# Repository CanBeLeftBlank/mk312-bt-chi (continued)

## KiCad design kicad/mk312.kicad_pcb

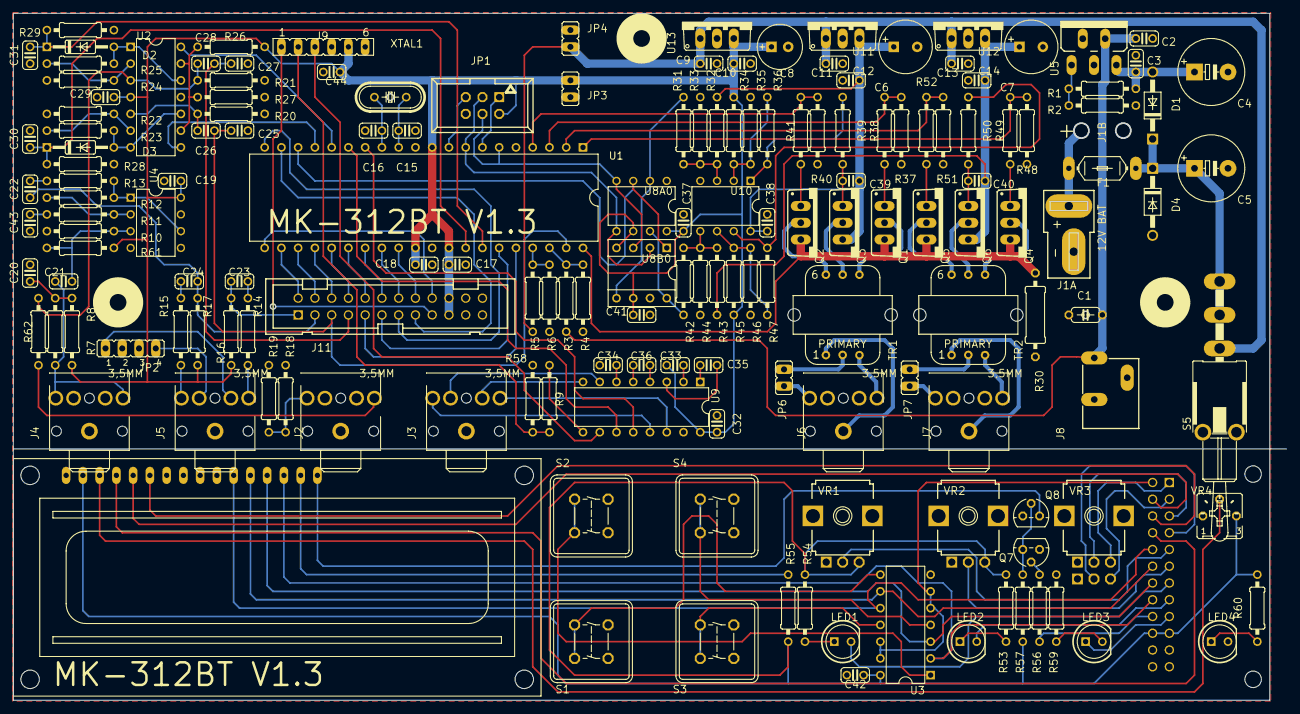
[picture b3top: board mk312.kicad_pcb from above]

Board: 2 copper layers, 193.0 x 104.1 mm, 170 parts (1 on the bottom side), 131 nets.

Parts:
@HOLE0, @HOLE1, @HOLE2, @HOLE3, @HOLE4: (no value)
C1: 10uF; C050-024X044
C2, C3, C9, C10, C11, C12, C13, C14, C17, C18, C19, C21, C26, C28, C29, C32, C37, C38, C39, C40, C41, C42, C44: 0.1uF; C025-024X044
C4, C5: 1000uF; E5-10,5
C6, C7: 470uF; E3,5-8
C8: 10uF; E2,5-7
C15, C16: 18pF; C025-024X044
C20, C22, C23, C24, C30, C31, C33, C34, C35, C36, C43: 1uF; C025-024X044
C25, C27: 1nF; C025-024X044
D1, D4: 1N4004; DO41-10
D2, D3: 1N4148DO35-10; DO35-10
F1: 1A POLY; LITTLEFUSE
J1: +12V BATTERY; DEANS
J2: REMOTE INPUT; STX3100
J3: LINK INPUT; STX3100
J4: MIC INPUT; STX3100
J5: LINE INPUT; STX3100
J6: OUTPUT A; STX3100
J7: OUTPUT B; STX3100
J8: VDC INPUT; POWER_JACK_SLOT
J9: RADIO INTERFACE; FE06
J10: 2524-; PAK100_2500-24
J11: FRONT PANEL; PAK100_2500-24
JP1: ISP; 057-006-1
JP2: AUX LINE IN; JP4
JP3: +5V; JP1
JP4: +12; JP1
JP6, JP7: JP1
LCD1: HD44780LCD-1602; LCD1602
LED1: OUTPUT A; LED5MM
LED2: OUTPUT B; LED5MM
LED3: RADIO; LED5MM
LED4: POWER; LED5MM
Q1, Q2, Q4, Q5: IRL520N; TO220V
Q3, Q6: IRF9Z24; TO220V
Q7, Q8: 2N3904; TO92
R1: 12K; 0207_10
R2: 1.2K; 0207_10
R3, R10, R20, R21, R27, R28, R29, R31, R32, R33, R34, R36, R37, R40, R42, R43, R44, R45, R47, R48, R51, R61: 100K; 0207_10
R4, R11, R16, R17, R22, R24: 20K; 0207_10
R5, R38, R39, R41, R49, R50, R52, R58: 10K; 0207_10
R6: 3.3K; 0207_10
R7, R8: 2.2K; 0207_10
R9, R13: 4.7K; 0207_10
R12, R23, R25, R26: 1M; 0207_10
R14, R15, R19, R62: 1K; 0207_10
R18, R56, R57: 1.5K; 0207_10
R30: 0.5R; 0309_12
R35, R46: 200K; 0207_10
R53, R54, R59, R60: 390; 0207_10
R55: 47; 0207_10
S1: OK; DTE6K
S2: MENU; DTE6K
S3: LEFT/DOWN; DTE6K
S4: RIGHT/UP; DTE6K
S5: POWER; LPV-1
TR1, TR2: 42TL004; 42TL
U1: ATMEGA16/32-P; DIL40
U2: LM324N; DIL14
U3: 4066N; DIL14
U4, U10: LM358N; DIL08
U5: LM2941T; TO220-5
U8A0: MAX548; DIL08
U8B0: LTC1661; SOCKET-08
U9: MAX232; DIL16
U11, U12: 7809TV; TO220V
U13: 7805TV; TO220V
VR1: LEVEL A; 9MM_SNAP-IN_POT
VR2: LEVEL B; 9MM_SNAP-IN_POT
VR3: MULTI-ADJ; DUAL_9MM_SNAP-IN_POT
VR4: LCD CONTRAST; B25P
XTAL1: 8.0 MHz; HC49_S

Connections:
+5V: C8.+, C10.1, C17.1, C18.1, C19.1, C29.1, C32.1, C33.1, C37.1, C41.1, C42.1, C44.1, J9.5, J10.19, J10.20, J11.19, J11.20, JP1.2, JP3.1, LCD1.2, R8.2, R16.2, R17.2, R18.2, R26.2, R34.2, R45.2, R53.2, R54.2, R55.2, R57.1, R60.2, R61.2, U1.10, U1.30, U1.32, U2.4, U3.14, U4.8, U8A0.6, U8A0.8, U8B0.4, U8B0.6, U9.16, U13.3, VR1.3, VR2.3, VR4.E
+8V: C6.+, C12.1, C38.1, C39.2, Q3.3, R32.2, U10.8, U11.3
+9V: C7.+, C14.1, C40.2, Q6.3, R43.2, U12.3
+12V: C9.1, C11.1, C13.1, JP4.1, R5.2, S5.1, U11.1, U12.1, U13.1
GND: C1.2, C2.2, C3.2, C4.-, C5.-, C6.-, C7.-, C8.-, C9.2, C10.2, C11.2, C12.2, C13.2, C14.2, C15.2, C16.2, C17.2, C18.2, C19.2, C20.2, C25.2, C27.2, C29.2, C30.2, C31.2, C32.2, C34.2, C37.2, C38.2, C41.2, C42.2, C43.2, C44.2, D4.A, J1.-, J2.1, J3.1, J4.1, J5.1, J8.GND@1, J8.GND@2, J9.4, J10.21, J10.22, J10.23, J10.24, J11.21, J11.22, J11.23, J11.24, JP1.6, JP2.2, JP2.3, JP3.2, JP4.2, LCD1.1, LED4.K, Q7.3, Q8.3, R2.1, R4.1, R6.1, R10.1, R19.1, R20.1, R21.1, R22.1, R24.2, R27.2, R28.2, R29.2, R30.1, R33.1, R35.1, R37.1, R40.1, R44.1, R46.1, R48.1, R51.1, R58.1, R59.2, S1.3, S1.4, S2.3, S2.4, S3.3, S3.4, S4.3, S4.4, S5.B, S5.B1, U1.11, U1.31, U2.11, U3.7, U4.4, U4.5, U5.2, U5.3, U8A0.1, U8B0.7, U9.15, U10.4, U11.2, U12.2, U13.2, VR1.1, VR1.CHASSIS2, VR2.1, VR2.CHASSIS2, VR3.1, VR3.1B, VR3.CHASSIS1, VR3.CHASSIS2, VR4.A
unnamed: J10.7, VR3.2B
unnamed: R5.1, R6.2, U1.37
unnamed: R3.1, R4.2, U1.38
unnamed: S1.1, S1.2, U3.8
unnamed: S3.1, S3.2, U3.11
unnamed: Q3.2, TR1.5
unnamed: S4.1, S4.2, U3.4
unnamed: Q6.2, TR2.5
unnamed: JP7.1, TR2.2
unnamed: J10.3, VR3.3B
unnamed: J10.9, VR1.2
unnamed: J10.11, VR2.2
unnamed: J10.1, VR3.3
unnamed: C28.2, R21.2, R62.2, U2.3
unnamed: J10.5, VR3.2
unnamed: J6.1, TR1.1
unnamed: C16.1, U1.13, XTAL1.2
unnamed: Q1.1, R38.2
unnamed: Q2.1, R41.2
unnamed: J7.2, JP7.2
unnamed: C39.1, Q3.1, R39.2
unnamed: R31.2, R32.1, R33.2, U10.3
unnamed: LED2.A, R53.1
unnamed: Q4.1, R49.2
unnamed: Q5.1, R52.2
unnamed: J7.1, TR2.1
unnamed: C40.1, Q6.1, R50.2
unnamed: R42.2, R43.1, R44.2, U10.5
unnamed: LED1.A, R54.1
unnamed: LCD1.3, VR4.S
unnamed: F1.1, J1.+
unnamed: C15.1, U1.12, XTAL1.1
unnamed: R9.2, U9.9
unnamed: Q1.2, TR1.4
unnamed: J6.5, TR1.3
unnamed: Q4.2, TR2.4
unnamed: J7.5, TR2.3
unnamed: Q5.2, TR2.6
unnamed: Q2.2, TR1.6
unnamed: R34.1, R35.2, R36.1, U10.2
unnamed: R45.1, R46.2, R47.1, U10.6
unnamed: R31.1, U8A0.2, U8B0.5
unnamed: R1.1, R2.2, U5.1
unnamed: J3.5, U9.14
unnamed: C3.1, C4.+, D1.A, R1.2, U5.5
unnamed: J3.2, U9.13
unnamed: LCD1.15, R55.1
unnamed: J6.2, JP6.2
unnamed: C43.1, R11.1
unnamed: J2.5, R62.1
unnamed: JP6.1, TR1.2
unnamed: C35.1, U9.1
unnamed: R24.1, R25.1, U2.2
unnamed: D2.A, R25.2, U2.1, U2.12
unnamed: J5.2, R15.1
unnamed: J5.5, R14.1
unnamed: C23.1, R14.2
unnamed: J2.2, R18.1, R19.2
unnamed: J5.4, JP2.1
unnamed: R22.2, R23.1, U2.6
unnamed: C35.2, U9.3
unnamed: R26.1, R27.1, U2.9, U2.13
unnamed: C26.2, R20.2, U2.5
unnamed: J5.3, JP2.4
unnamed: C24.1, R15.2
unnamed: C36.2, U9.5
unnamed: C36.1, U9.4
unnamed: J9.2, R9.1, R58.2
unnamed: D3.A, R23.2, U2.7, U2.10
unnamed: C34.1, U9.6
unnamed: C21.1, J4.2, J4.5, R7.1
unnamed: C20.1, R7.2, R8.1
unnamed: C21.2, R10.2, R61.1, U4.3
unnamed: R11.2, R12.1, U4.2
unnamed: R12.2, R13.1, U4.1, U4.6
unnamed: C22.2, R13.2
unnamed: C33.2, U9.2
unnamed: C5.+, D1.C, D4.C, F1.2, S5.2, S5.3
unnamed: LED3.K, R59.1
unnamed: S2.1, S2.2, U3.1
unnamed: LED4.A, R60.1
unnamed: Q7.2, R56.1
unnamed: Q7.1, Q8.2, R57.2
unnamed: LCD1.16, Q8.1
unnamed: R42.1, U8A0.7, U8B0.8
unnamed: J10.17, LED3.A
unnamed: J3.4, U9.8
unnamed: J3.3, U9.7
unnamed: J9.3, U9.10
PA0: Q1.3, Q2.3, Q4.3, Q5.3, R30.2, U1.40
PA1: C25.1, C26.1, J11.5, U1.39
PA4: J11.9, U1.36
PA5: J11.11, U1.35
PA6: C31.1, D2.C, R29.1, U1.34
PA7: C30.1, D3.C, R28.1, U1.33
PB0: R48.2, R49.1, U1.1
PB1: R51.2, R52.1, U1.2
PB2: R37.2, R38.1, U1.3
PB3: R40.2, R41.1, U1.4
PB5: JP1.4, U1.6, U8A0.4, U8B0.3
PB6: JP1.1, U1.7
PB7: JP1.3, U1.8, U8A0.5, U8B0.2
PC0: J10.2, J11.2, U1.22, U3.5, U3.6, U3.12, U3.13
PC1: J10.4, J11.4, LCD1.5, U1.23
PC2: J10.6, J11.6, LCD1.6, U1.24
PC3: J10.8, J11.8, LCD1.4, U1.25
PC4: J10.10, J11.10, LCD1.11, U1.26, U3.10
PC5: J10.12, J11.12, LCD1.12, U1.27, U3.9
PC6: J10.14, J11.14, LCD1.13, U1.28, U3.3
PC7: J10.16, J11.16, LCD1.14, U1.29, U3.2
PD0: U1.14, U9.12
PD1: U1.15, U9.11
PD2: U1.16, U2.14
PD3: U1.17, U2.8
PD5: J10.15, J11.15, LED2.K, U1.19
PD6: J10.13, J11.13, LED1.K, U1.20
PD7: J10.18, J11.18, R56.2, U1.21
PFET_A: R36.2, R39.1, U10.1
PFET_B: R47.2, R50.1, U10.7
RB4: C27.1, C28.1, J11.7
RB9: C22.1, C24.2, J11.3, R17.1
RB10: C23.2, J11.1, R16.1
RESET: JP1.5, U1.9
STATE: J9.1, J11.17
V+: C1.1, C2.1, J8.PWR, R3.2, U5.4
~CS: U1.18, U8A0.3, U8B0.1

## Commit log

2022-07-30 Cleanup, removal of many duplicate files, re-organize files
2022-07-30 Import of 1.3R version into KiCad, no structural changes. Also made a small document with the changes between 1.3B and 1.3R
2022-07-30 Conversion of display print to KiCad components; still attached to main board
2022-07-31 Conversion of 1.3R version to KiCad!
2022-08-01 Fixing mounting holes for display print
2022-08-01 Tiny fixups on mainboard: mounting holes and one audio jack
2022-08-01 Converted front panel as well
2022-08-07 Bringing mainboard up to par with V1.4 schematics based on images. Rerouted a few lines since they could not pass below the MOSFETs due to a different footprint/pad size.
2022-08-09 Display print is now on parity with V1.4, but has been re-routed. U3 has also been rotated 180 degrees. Some components have been moved to other places as well
2022-08-10 A few more datasheets
2022-08-10 Brought component numbers back in line with the original schematics
2022-08-10 Adding footprint for combined Xicon 42TL or 42TU transformer; has dual mounting holes.
2022-08-10 Putting in new combined footprint for transformer. Updated F.Fab layer with component values in the correct place
2022-08-10 Moving text to silkscreen layer
2022-08-10 Update of the README with a bit more sensible info.
2022-08-13 A bit of cleanup, showing type of some OpAmps and clarification of wiring around U4
2022-08-14 Removing copied schematics from mainboard.
2022-08-14 Cleaning up F.Fab layer, putting values at the right places.
2022-09-04 Add building instructions and updated BOM
2022-09-04 Fixed footprint for powerbus connector. Bumped version to 1.4.1.
2022-09-04 Datasheets for LCD and on/off switch
2022-09-04 Two small fixups for the display & frontend. Made mounting holes in display PCB larger. Moved LCD window slightly to the right on the front panel.
2022-09-05 Updated build instructions for display/front panel
2022-09-16 Fixing position of R48/R49 on F.Fab layer
2022-09-16 Small textual changes in BOM and building instructions
2022-12-17 Fixed labels of R37 and R38 on Fab layer.
2022-12-29 Increase clearance around primary side of transformers. Moved name and version to a visible spot on the PCB silkscreen.
2022-12-29 Cleanup of old gerber files
2022-12-29 Version 1.4.2 Gerber files and revision history
2022-12-29 Some pictures of the first 1.4-Chi version
2022-12-29 Removing old Eagle files and BOMs.
2022-12-29 Patched firmware for LCD
2022-12-29 Updated the README to include all the information regarding getting parts and building. Removed old information.
2022-12-29 More cleanup of old Eagle stuff
2023-01-02 Added a bit of documentation about charging.
